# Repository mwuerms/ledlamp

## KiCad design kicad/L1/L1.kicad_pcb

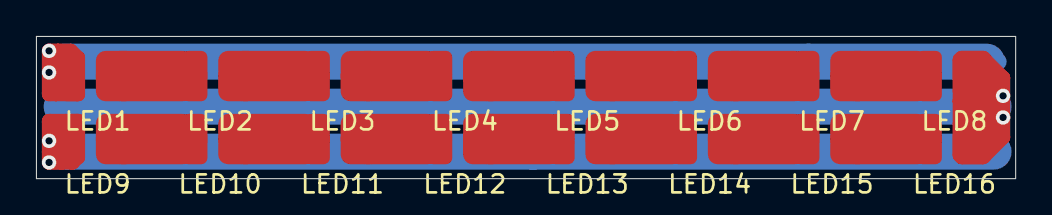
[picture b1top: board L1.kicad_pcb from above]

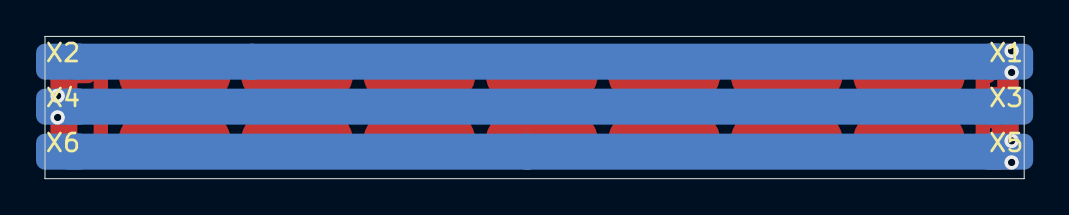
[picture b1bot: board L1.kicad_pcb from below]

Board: 2 copper layers, 54.4 x 7.9 mm, 22 parts (6 on the bottom side), 17 nets.

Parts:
LED1, LED2, LED3, LED4, LED5, LED6, LED7, LED8, LED9, LED10, LED11, LED12, LED13, LED14, LED15, LED16: JE2835
X1, X2, X3, X4, X5, X6: TP

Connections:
GND: LED8.1, LED16.1, X3.1, X4.1
unnamed: LED1.1, LED2.2
unnamed: LED2.1, LED3.2
unnamed: LED3.1, LED4.2
unnamed: LED4.1, LED5.2
unnamed: LED5.1, LED6.2
unnamed: LED6.1, LED7.2
unnamed: LED7.1, LED8.2
unnamed: LED10.1, LED11.2
unnamed: LED9.1, LED10.2
unnamed: LED11.1, LED12.2
unnamed: LED12.1, LED13.2
unnamed: LED13.1, LED14.2
unnamed: LED14.1, LED15.2
unnamed: LED15.1, LED16.2
VDD: LED1.2, X1.1, X2.1
VDDF: LED9.2, X5.1, X6.1

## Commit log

2021-11-25 added pcb
2021-11-28 L1: in eagle7, ready to order
